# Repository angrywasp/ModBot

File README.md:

# ModBot
Hardware and firmware for a modular robotics system

## Requirements 

PropGCC: https://github.com/angrywasp/propeller-gcc-windows  
Get two command line tools:  
[BSI, the BasicScript interpreter](https://github/com/angrywasp/basicscript). Scripts are written in BasicScript. Follow the link to learn more
PropTool. A basic command line tool for programming the Propeller chip. Compatible with official and unofficial propeller programming hardware
```
dotnet tool install -g AngryWasp.BasicScript.Interpreter
dotnet tool install -g AngryWasp.PropTool
```

Then build the framework
```powershell
bsi ./make.bs --% --run clean()
bsi ./make.bs --% --run buildFramework()
```

Hardware Notes: mn     mn

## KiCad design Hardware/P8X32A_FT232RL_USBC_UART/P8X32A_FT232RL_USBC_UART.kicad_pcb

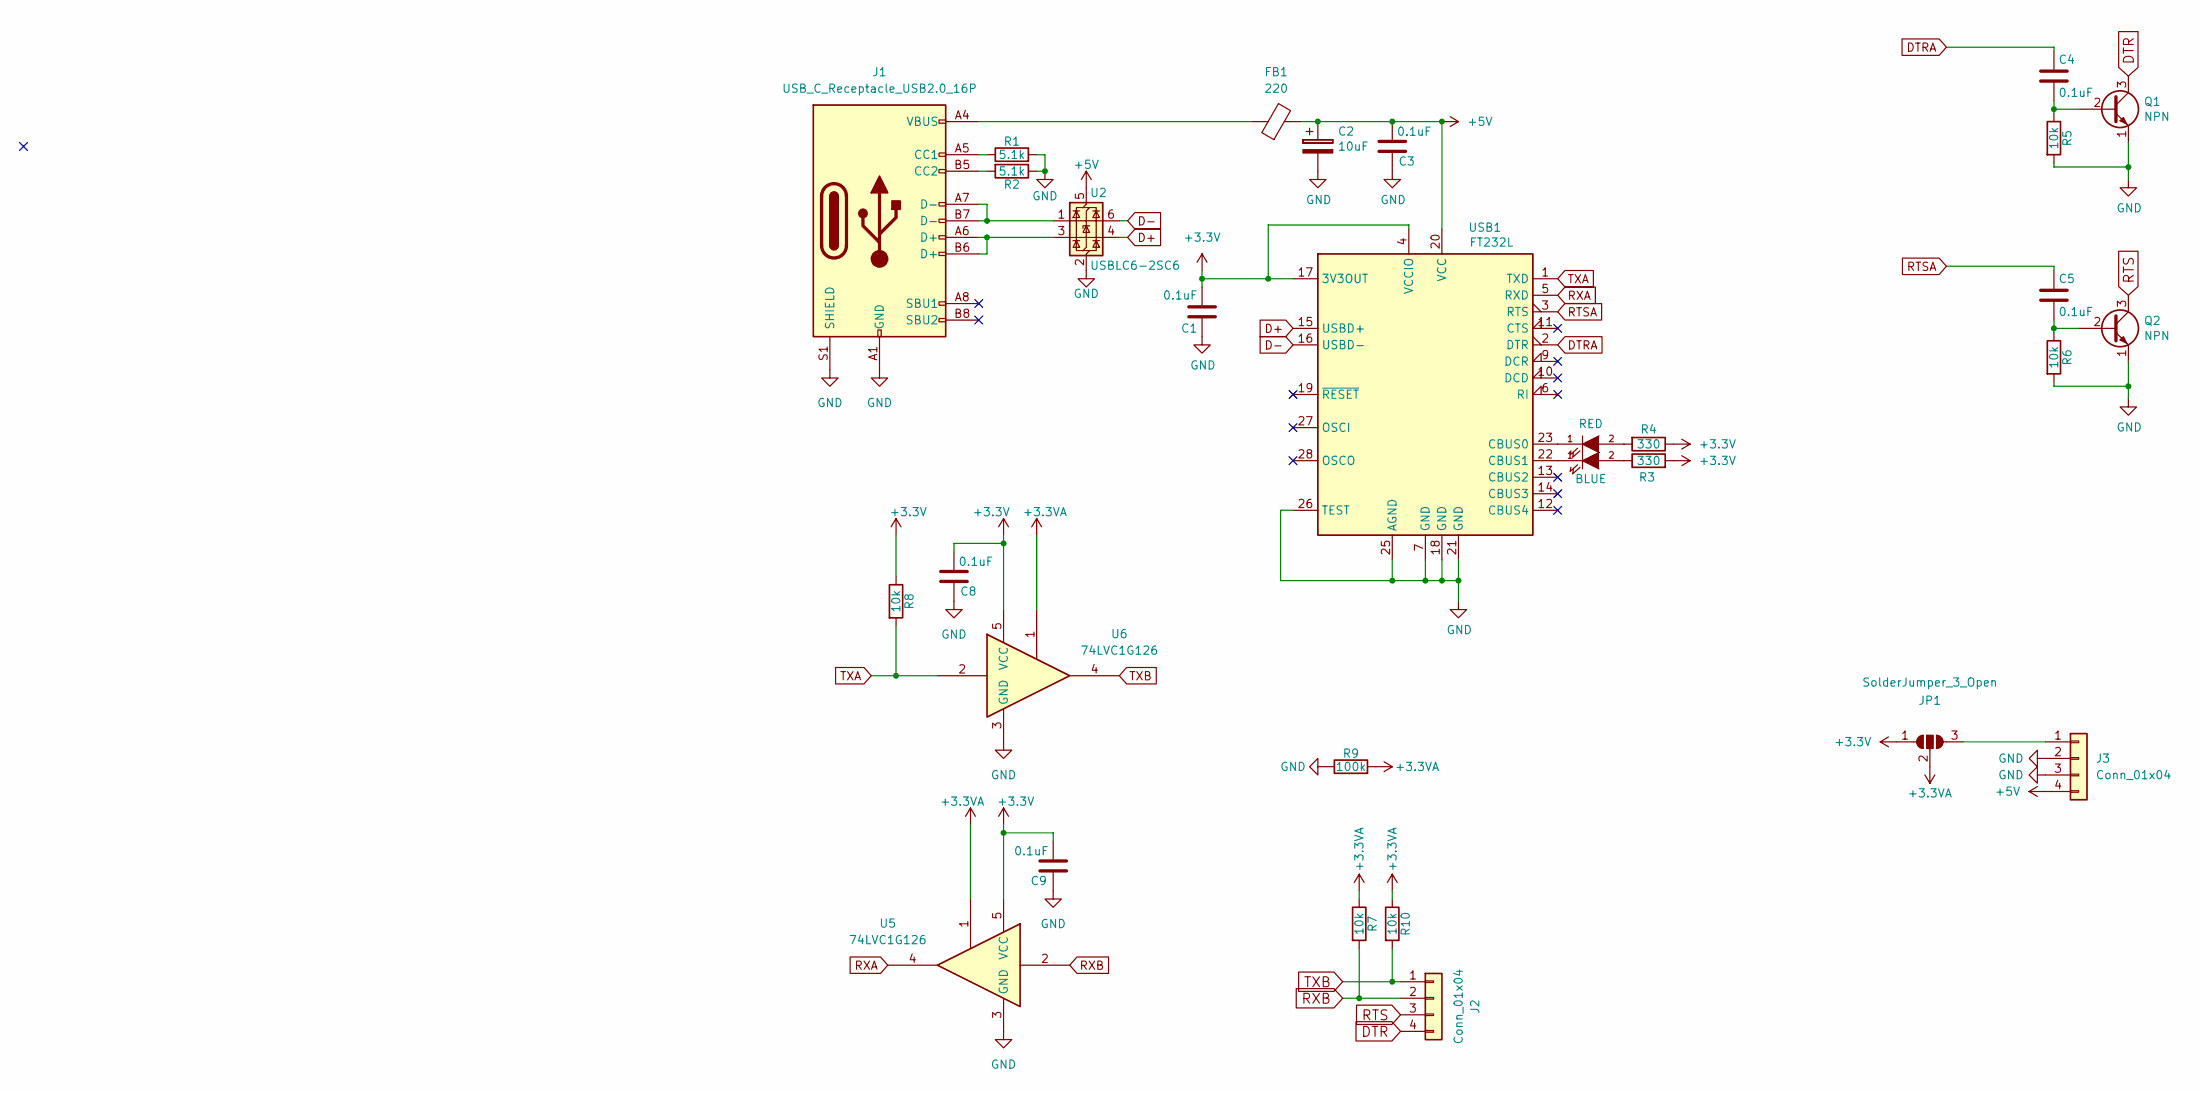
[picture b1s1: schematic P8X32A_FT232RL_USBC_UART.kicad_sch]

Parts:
C1, C3, C4, C5, C8, C9: 0.1uF; C_0805_2012Metric_Pad1.18x1.45mm_HandSolder
C2: 10uF; CP_EIA-3216-18_Kemet-A_HandSolder
D2: BLUE; LED_0805_2012Metric_Pad1.15x1.40mm_HandSolder
D3: RED; LED_0805_2012Metric_Pad1.15x1.40mm_HandSolder
FB1: 220; R_0805_2012Metric_Pad1.20x1.40mm_HandSolder
J1: USB_C_Receptacle_USB2.0_16P; USB_C_Receptacle_HCTL_HC-TYPE-C-16P-01A
J2, J3: Conn_01x04; PinSocket_1x04_P2.54mm_Vertical
JP1: SolderJumper_3_Open; SolderJumper-3_P1.3mm_Open_RoundedPad1.0x1.5mm
Q1, Q2: NPN; SOT-23_Handsoldering
R1, R2: 5.1k; R_0805_2012Metric_Pad1.20x1.40mm_HandSolder
R3, R4: 330; R_0805_2012Metric_Pad1.20x1.40mm_HandSolder
R5, R6, R7, R8, R10: 10k; R_0805_2012Metric_Pad1.20x1.40mm_HandSolder
R9: 100k; R_0805_2012Metric_Pad1.20x1.40mm_HandSolder
U2: USBLC6-2SC6; SOT-23-6
U5, U6: 74LVC1G126; SOT-23-5
USB1: FT232L; SSOP-28_5.3x10.2mm_P0.65mm

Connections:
+3.3V: C1.2, C8.2, C9.2, JP1.1 (A), R3.2, R4.1, R8.1, U5.5 (VCC), U6.5 (VCC), USB1.4 (VCCIO), USB1.17 (3V3OUT)
+3.3VA: JP1.2 (C), R7.1, R9.2, R10.1, U5.1, U6.1
+5V: C2.1, C3.2, FB1.2, J3.4, U2.5 (VBUS), USB1.20 (VCC)
D+: U2.4 (I/O2), USB1.15 (USBD+)
D-: U2.6 (I/O1), USB1.16 (USBD-)
DTR: J2.4, Q1.3 (C)
DTRA: C4.1, USB1.2 (DTR)
GND: C1.1, C2.2, C3.1, C8.1, C9.1, J1.A1 (GND), J1.A12 (GND), J1.B1 (GND), J1.B12 (GND), J1.S1 (SHIELD), J3.2, J3.3, Q1.1 (E), Q2.1 (E), R1.2, R2.1, R5.2, R6.2, R9.1, U2.2 (GND), U5.3 (GND), U6.3 (GND), USB1.7 (GND), USB1.18 (GND), USB1.21 (GND), USB1.25 (AGND), USB1.26 (TEST)
unnamed: D2.2 (A), R3.1
unnamed: D2.1 (K), USB1.22 (CBUS1)
unnamed: D3.2 (A), R4.2
unnamed: D3.1 (K), USB1.23 (CBUS0)
unnamed: FB1.1, J1.A4 (VBUS), J1.A9 (VBUS), J1.B4 (VBUS), J1.B9 (VBUS)
unnamed: J1.A5 (CC1), R1.1
unnamed: J1.B5 (CC2), R2.2
unnamed: J1.A6 (D+), J1.B6 (D+), U2.3 (I/O2)
unnamed: J1.A7 (D-), J1.B7 (D-), U2.1 (I/O1)
unnamed: J3.1, JP1.3 (B)
unnamed: C4.2, Q1.2 (B), R5.1
unnamed: C5.2, Q2.2 (B), R6.1
RTS: J2.3, Q2.3 (C)
RTSA: C5.1, USB1.3 (RTS)
RXA: U5.4, USB1.5 (RXD)
RXB: J2.2, R7.2, U5.2
TXA: R8.2, U6.2, USB1.1 (TXD)
TXB: J2.1, R10.2, U6.4

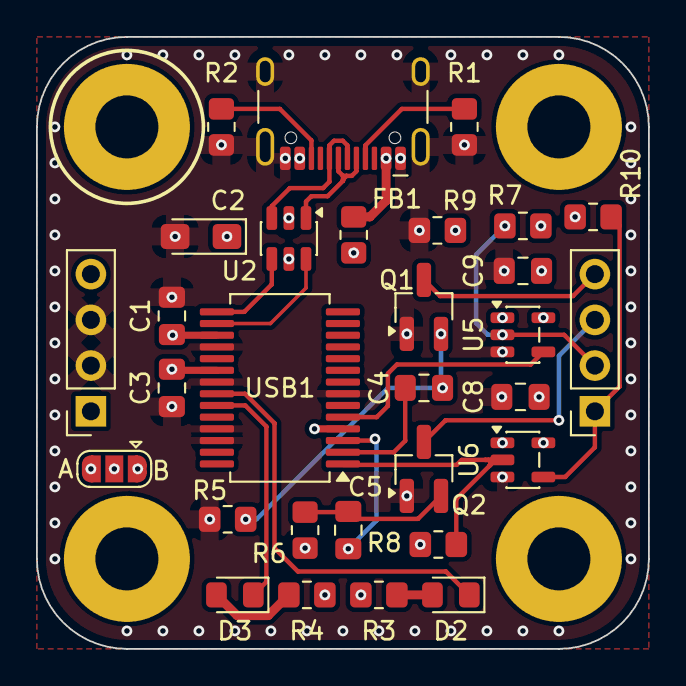
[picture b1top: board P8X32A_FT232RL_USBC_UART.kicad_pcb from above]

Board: 4 copper layers, 34.0 x 34.0 mm, 30 parts (0 on the bottom side), 26 nets.

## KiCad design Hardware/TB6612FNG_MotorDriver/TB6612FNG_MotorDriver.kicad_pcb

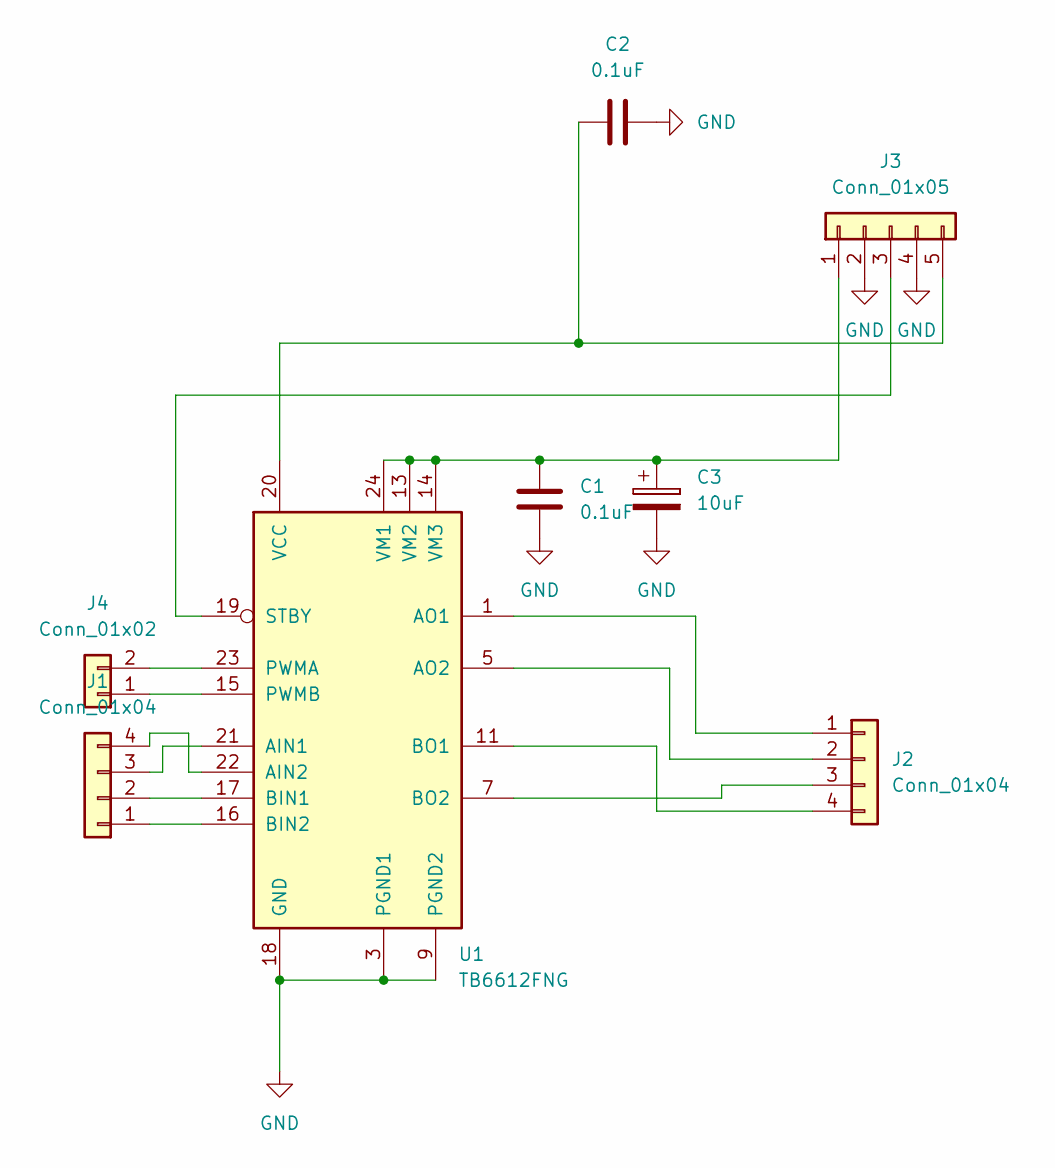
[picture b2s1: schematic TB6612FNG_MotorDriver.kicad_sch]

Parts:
C1, C2: 0.1uF; C_0805_2012Metric_Pad1.18x1.45mm_HandSolder
C3: 10uF; CP_Elec_4x3
J1, J2: Conn_01x04; PinHeader_1x04_P2.54mm_Vertical
J3: Conn_01x05; PinHeader_1x05_P2.54mm_Vertical
J4: Conn_01x02; PinHeader_1x02_P2.54mm_Vertical
U1: TB6612FNG; SSOP-24_5.3x8.2mm_P0.65mm

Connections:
GND: C1.2, C2.2, C3.2, J3.2, J3.4, U1.3 (PGND1), U1.4 (PGND1), U1.9 (PGND2), U1.10 (PGND2), U1.18 (GND)
unnamed: J1.1, U1.16 (BIN2)
unnamed: J1.2, U1.17 (BIN1)
unnamed: J1.3, U1.21 (AIN1)
unnamed: J1.4, U1.22 (AIN2)
unnamed: J2.1, U1.1 (AO1), U1.2 (AO1)
unnamed: J2.2, U1.5 (AO2), U1.6 (AO2)
unnamed: J2.3, U1.7 (BO2), U1.8 (BO2)
unnamed: J2.4, U1.11 (BO1), U1.12 (BO1)
unnamed: C1.1, C3.1, J3.1, U1.13 (VM2), U1.14 (VM3), U1.24 (VM1)
unnamed: J3.3, U1.19 (STBY)
unnamed: C2.1, J3.5, U1.20 (VCC)
unnamed: J4.1, U1.15 (PWMB)
unnamed: J4.2, U1.23 (PWMA)

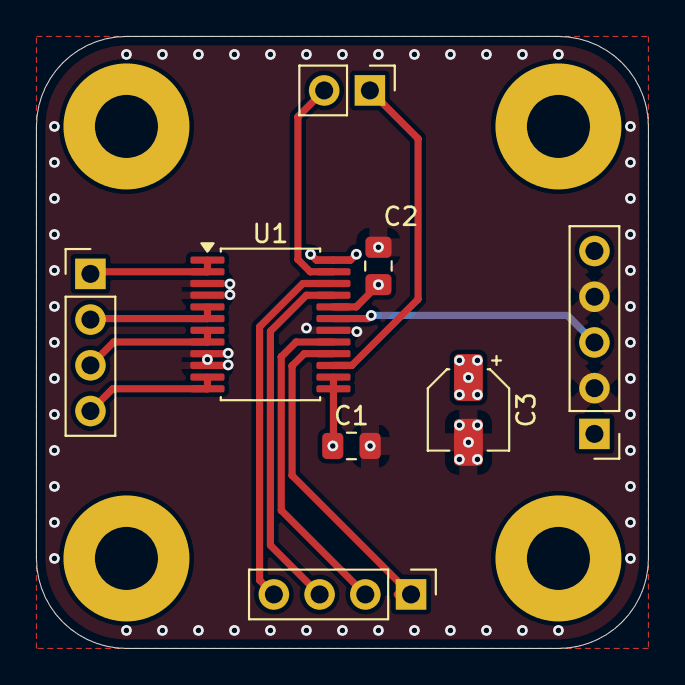
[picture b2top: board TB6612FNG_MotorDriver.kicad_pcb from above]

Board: 4 copper layers, 34.0 x 34.0 mm, 8 parts (0 on the bottom side), 14 nets.

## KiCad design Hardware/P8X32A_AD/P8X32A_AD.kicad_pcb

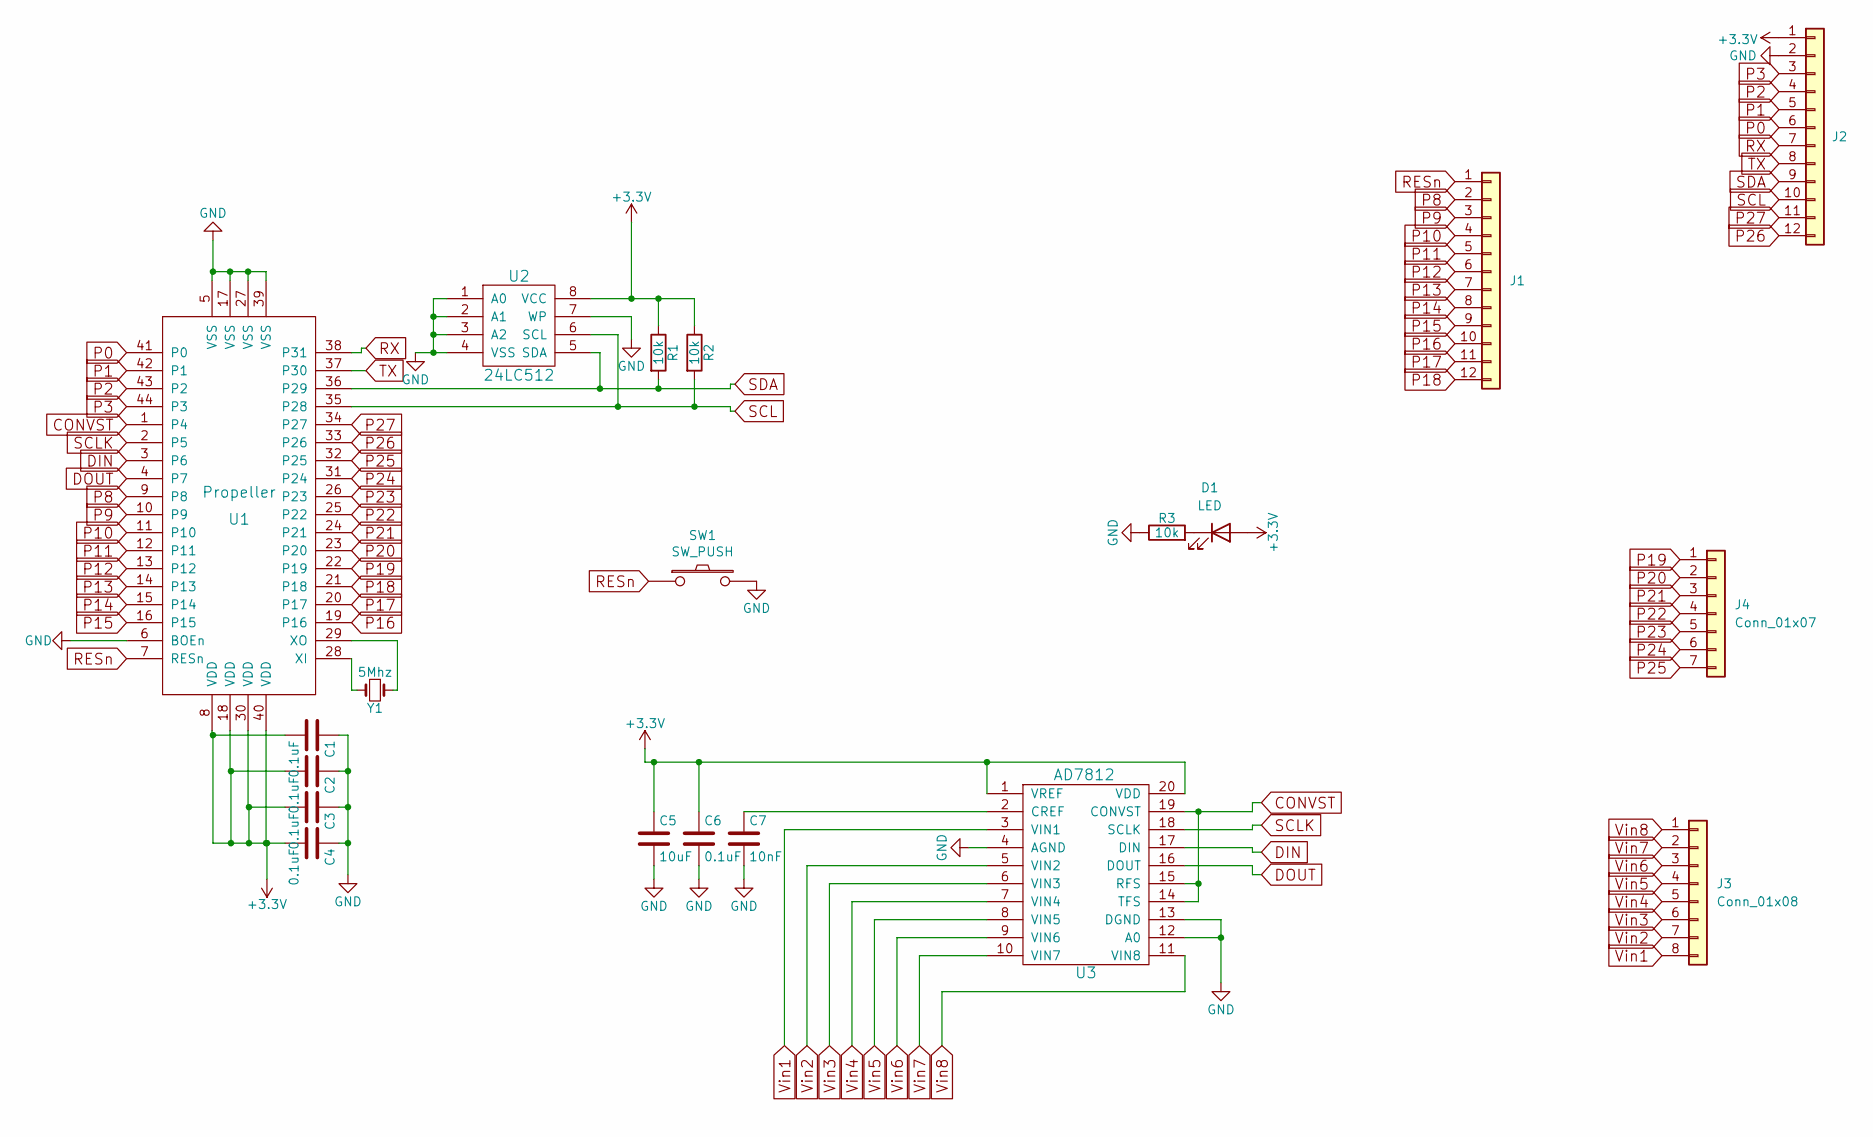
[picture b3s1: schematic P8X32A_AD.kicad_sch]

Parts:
C1, C2, C3, C4, C6: 0.1uF; C_0805_2012Metric_Pad1.18x1.45mm_HandSolder
C5: 10uF; C_0805_2012Metric_Pad1.18x1.45mm_HandSolder
C7: 10nF; C_0805_2012Metric_Pad1.18x1.45mm_HandSolder
D1: LED; LED_0805_2012Metric_Pad1.15x1.40mm_HandSolder
J1, J2: Conn_01x12; PinHeader_1x12_P2.54mm_Vertical
J3: Conn_01x08; PinHeader_1x08_P2.54mm_Vertical
J4: Conn_01x07; PinHeader_1x07_P2.54mm_Vertical
R1, R2, R3: 10k; R_0805_2012Metric_Pad1.20x1.40mm_HandSolder
SW1: SW_PUSH; SW_SPST
U1: Propeller; LQFP-44_10x10mm_P0.8mm
U2: 24LC512; SOIC-8_5.3x5.3mm_P1.27mm
U3: AD7812; Infineon_SOIC-20W_7.6x12.8mm_P1.27mm
Y1: 5Mhz; Crystal_SMD_HC49-SD

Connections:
+3.3V: C1.2, C2.2, C3.2, C4.2, C5.1, C6.1, D1.2 (A), J2.1, R1.1, R2.1, U1.8 (VDD), U1.18 (VDD), U1.30 (VDD), U1.40 (VDD), U2.8 (VCC), U3.1 (VREF), U3.20 (VDD)
CONVST: U1.1 (P4), U3.14 (TFS), U3.15 (RFS), U3.19 (CONVST)
DIN: U1.3 (P6), U3.17 (DIN)
DOUT: U1.4 (P7), U3.16 (DOUT)
GND: C1.1, C2.1, C3.1, C4.1, C5.2, C6.2, C7.2, J2.2, R3.1, SW1.2, U1.5 (VSS), U1.6 (BOEn), U1.17 (VSS), U1.27 (VSS), U1.39 (VSS), U2.1 (A0), U2.2 (A1), U2.3 (A2), U2.4 (VSS), U2.7 (WP), U3.4 (AGND), U3.12 (A0), U3.13 (DGND)
unnamed: D1.1 (K), R3.2
unnamed: U1.28 (XI), Y1.2
unnamed: U1.29 (XO), Y1.1
unnamed: C7.1, U3.2 (CREF)
P0: J2.6, U1.41 (P0)
P1: J2.5, U1.42 (P1)
P2: J2.4, U1.43 (P2)
P3: J2.3, U1.44 (P3)
P8: J1.2, U1.9 (P8)
P9: J1.3, U1.10 (P9)
P10: J1.4, U1.11 (P10)
P11: J1.5, U1.12 (P11)
P12: J1.6, U1.13 (P12)
P13: J1.7, U1.14 (P13)
P14: J1.8, U1.15 (P14)
P15: J1.9, U1.16 (P15)
P16: J1.10, U1.19 (P16)
P17: J1.11, U1.20 (P17)
P18: J1.12, U1.21 (P18)
P19: J4.1, U1.22 (P19)
P20: J4.2, U1.23 (P20)
P21: J4.3, U1.24 (P21)
P22: J4.4, U1.25 (P22)
P23: J4.5, U1.26 (P23)
P24: J4.6, U1.31 (P24)
P25: J4.7, U1.32 (P25)
P26: J2.12, U1.33 (P26)
P27: J2.11, U1.34 (P27)
RESn: J1.1, SW1.1, U1.7 (RESn)
RX: J2.7, U1.38 (P31)
SCL: J2.10, R2.2, U1.35 (P28), U2.6 (SCL)
SCLK: U1.2 (P5), U3.18 (SCLK)
SDA: J2.9, R1.2, U1.36 (P29), U2.5 (SDA)
TX: J2.8, U1.37 (P30)
Vin1: J3.8, U3.3 (VIN1)
Vin2: J3.7, U3.5 (VIN2)
Vin3: J3.6, U3.6 (VIN3)
Vin4: J3.5, U3.7 (VIN4)
Vin5: J3.4, U3.8 (VIN5)
Vin6: J3.3, U3.9 (VIN6)
Vin7: J3.2, U3.10 (VIN7)
Vin8: J3.1, U3.11 (VIN8)

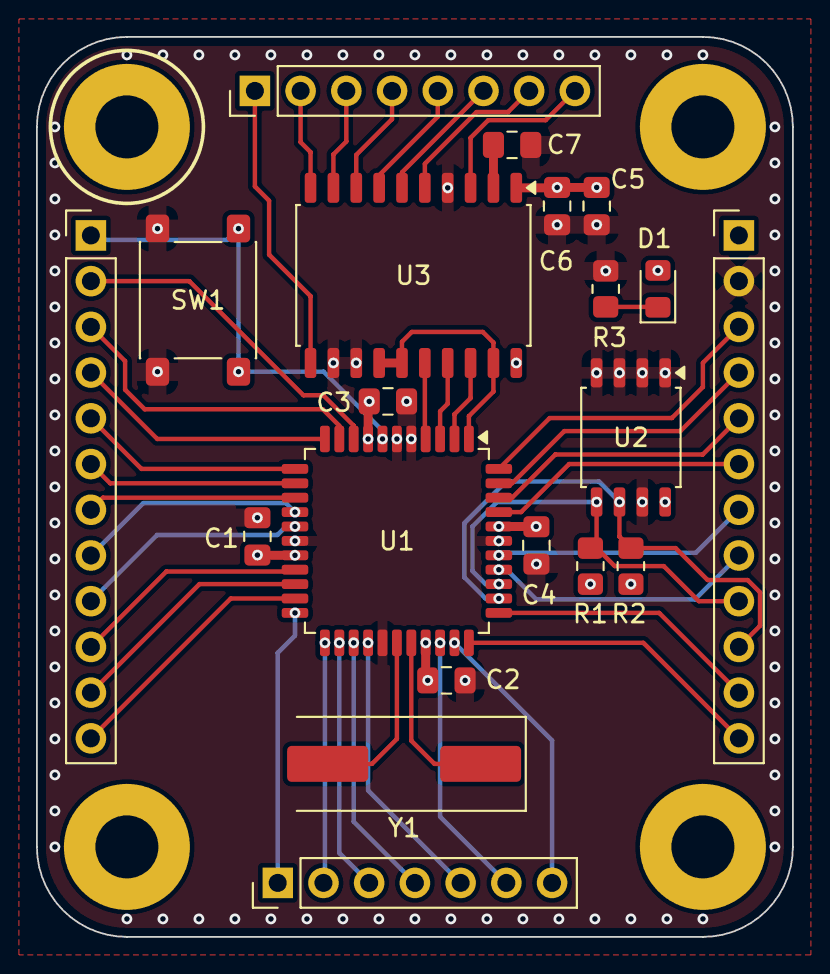
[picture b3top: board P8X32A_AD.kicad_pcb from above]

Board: 4 copper layers, 42.0 x 50.0 mm, 20 parts (0 on the bottom side), 47 nets.

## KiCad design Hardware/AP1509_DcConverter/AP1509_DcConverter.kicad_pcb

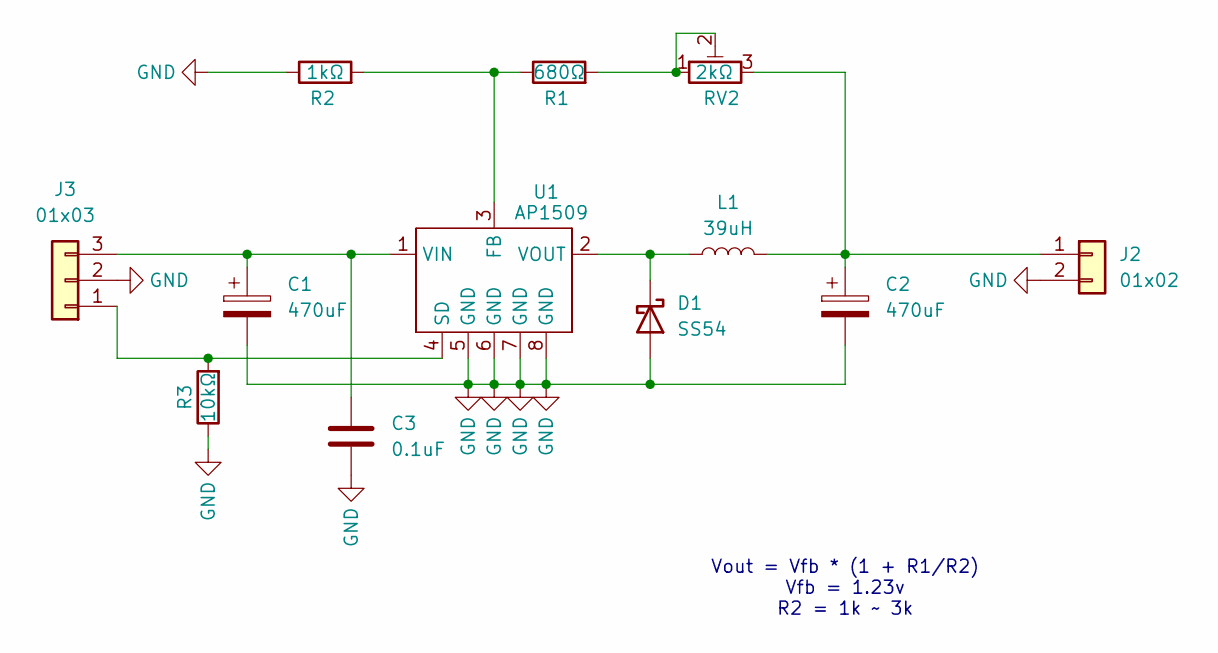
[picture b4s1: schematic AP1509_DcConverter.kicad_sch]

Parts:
C1, C2: 470uF; CP_Elec_8x10.5
C3: 0.1uF; C_0805_2012Metric_Pad1.18x1.45mm_HandSolder
D1: SS54; D_SMB_Handsoldering
J2: 01x02; PinHeader_1x02_P2.54mm_Vertical
J3: 01x03; PinHeader_1x03_P2.54mm_Vertical
L1: 39uH; L_APV_APH0630
R1: 680Ω; R_0805_2012Metric_Pad1.20x1.40mm_HandSolder
R2: 1kΩ; R_0805_2012Metric_Pad1.20x1.40mm_HandSolder
R3: 10kΩ; R_0805_2012Metric_Pad1.20x1.40mm_HandSolder
RV2: 2kΩ; Potentiometer_Bourns_3224W_Vertical
U1: AP1509; SOP-8_3.76x4.96mm_P1.27mm

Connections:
GND: C1.2, C2.2, C3.2, D1.2 (A), J2.2, J3.2, R2.1, R3.1, U1.5 (GND), U1.6 (GND), U1.7 (GND), U1.8 (GND)
unnamed: D1.1 (K), L1.1, U1.2 (VOUT)
unnamed: C2.1, J2.1, L1.2, RV2.3
unnamed: J3.1, R3.2, U1.4 (SD)
unnamed: C1.1, C3.1, J3.3, U1.1 (VIN)
unnamed: R1.2, RV2.1, RV2.2
unnamed: R1.1, R2.2, U1.3 (FB)

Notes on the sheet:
Vout = Vfb * (1 + R1/R2) Vfb = 1.23v R2 = 1k ~ 3k

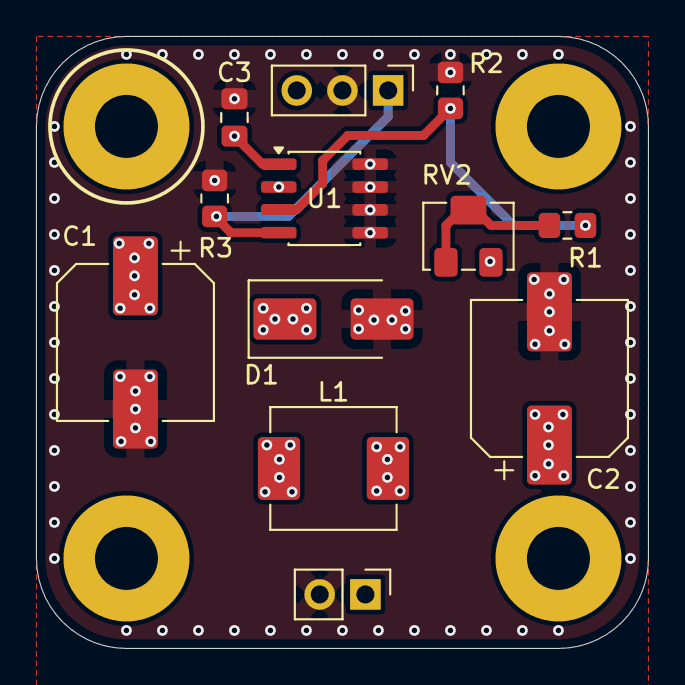
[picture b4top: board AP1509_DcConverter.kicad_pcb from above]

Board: 4 copper layers, 34.0 x 34.0 mm, 12 parts (0 on the bottom side), 7 nets.

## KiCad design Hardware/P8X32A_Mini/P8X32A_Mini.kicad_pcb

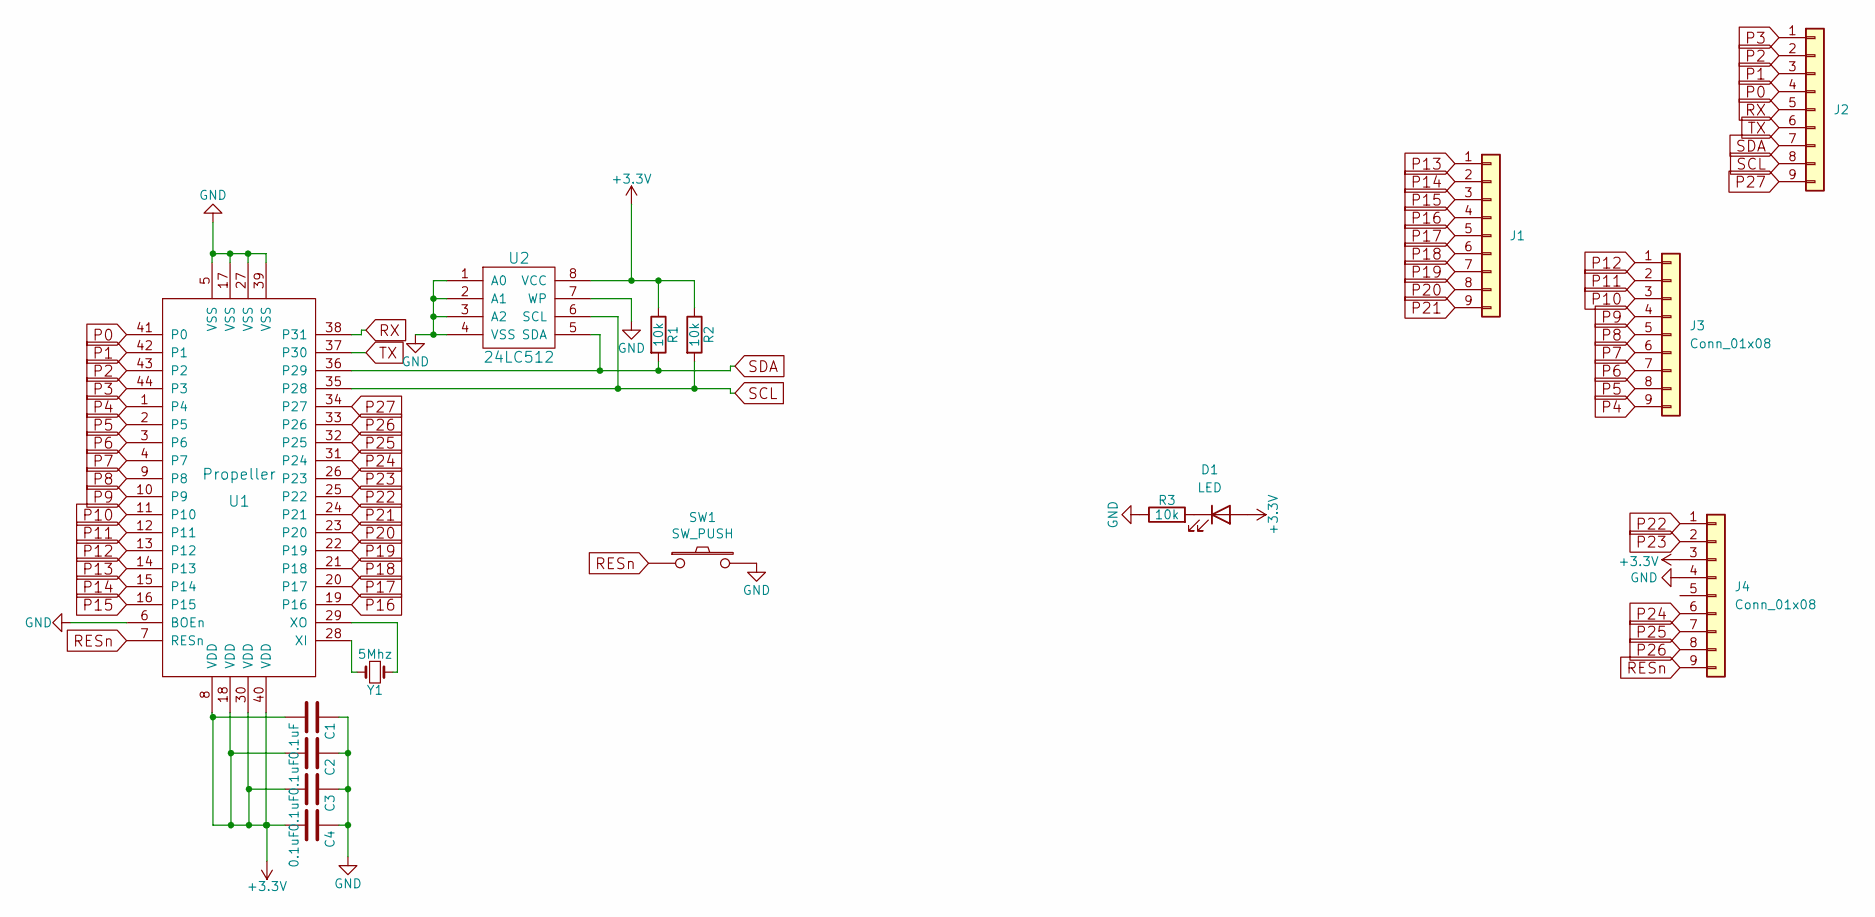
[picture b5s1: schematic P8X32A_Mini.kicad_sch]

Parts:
C1, C2, C3, C4: 0.1uF; C_0805_2012Metric_Pad1.18x1.45mm_HandSolder
D1: LED; LED_0805_2012Metric_Pad1.15x1.40mm_HandSolder
J1, J2: Conn_01x09; PinHeader_1x09_P2.54mm_Vertical
J3, J4: Conn_01x08; PinHeader_1x09_P2.54mm_Vertical
R1, R2, R3: 10k; R_0805_2012Metric_Pad1.20x1.40mm_HandSolder
SW1: SW_PUSH; SW_SPST
U1: Propeller; LQFP-44_10x10mm_P0.8mm
U2: 24LC512; SOIC-8_5.3x5.3mm_P1.27mm
Y1: 5Mhz; Crystal_SMD_HC49-SD

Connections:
+3.3V: C1.2, C2.2, C3.2, C4.2, D1.2 (A), J4.3, R1.1, R2.1, U1.8 (VDD), U1.18 (VDD), U1.30 (VDD), U1.40 (VDD), U2.8 (VCC)
GND: C1.1, C2.1, C3.1, C4.1, J4.4, R3.1, SW1.2, U1.5 (VSS), U1.6 (BOEn), U1.17 (VSS), U1.27 (VSS), U1.39 (VSS), U2.1 (A0), U2.2 (A1), U2.3 (A2), U2.4 (VSS), U2.7 (WP)
unnamed: D1.1 (K), R3.2
unnamed: U1.28 (XI), Y1.2
unnamed: U1.29 (XO), Y1.1
P0: J2.4, U1.41 (P0)
P1: J2.3, U1.42 (P1)
P2: J2.2, U1.43 (P2)
P3: J2.1, U1.44 (P3)
P4: J3.9, U1.1 (P4)
P5: J3.8, U1.2 (P5)
P6: J3.7, U1.3 (P6)
P7: J3.6, U1.4 (P7)
P8: J3.5, U1.9 (P8)
P9: J3.4, U1.10 (P9)
P10: J3.3, U1.11 (P10)
P11: J3.2, U1.12 (P11)
P12: J3.1, U1.13 (P12)
P13: J1.1, U1.14 (P13)
P14: J1.2, U1.15 (P14)
P15: J1.3, U1.16 (P15)
P16: J1.4, U1.19 (P16)
P17: J1.5, U1.20 (P17)
P18: J1.6, U1.21 (P18)
P19: J1.7, U1.22 (P19)
P20: J1.8, U1.23 (P20)
P21: J1.9, U1.24 (P21)
P22: J4.1, U1.25 (P22)
P23: J4.2, U1.26 (P23)
P24: J4.6, U1.31 (P24)
P25: J4.7, U1.32 (P25)
P26: J4.8, U1.33 (P26)
P27: J2.9, U1.34 (P27)
RESn: J4.9, SW1.1, U1.7 (RESn)
RX: J2.5, U1.38 (P31)
SCL: J2.8, R2.2, U1.35 (P28), U2.6 (SCL)
SDA: J2.7, R1.2, U1.36 (P29), U2.5 (SDA)
TX: J2.6, U1.37 (P30)

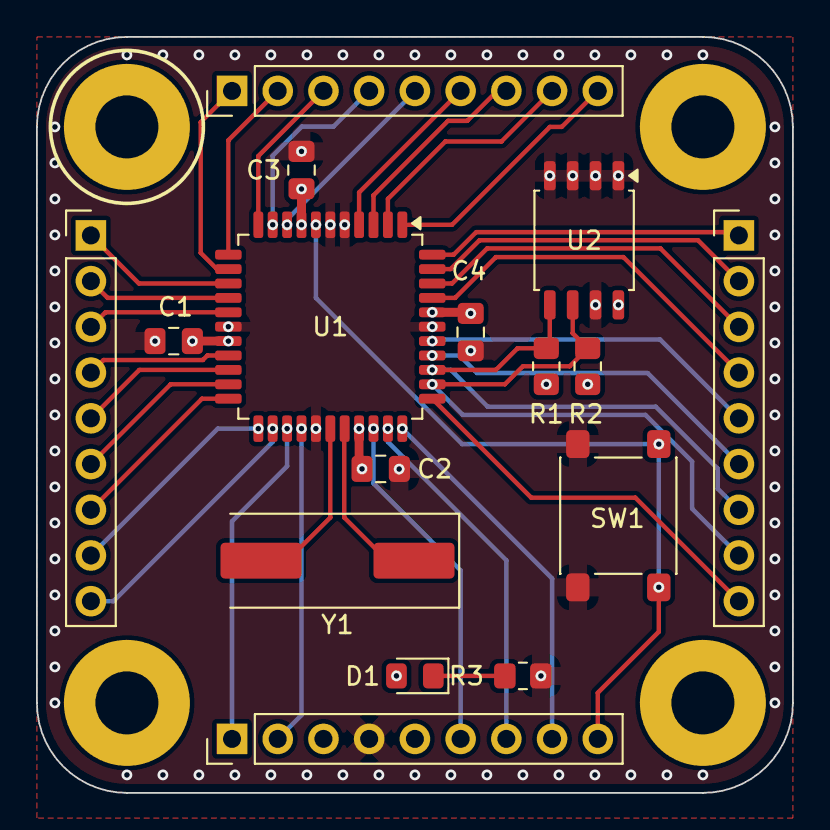
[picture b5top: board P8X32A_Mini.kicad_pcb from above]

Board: 4 copper layers, 42.0 x 42.0 mm, 16 parts (0 on the bottom side), 38 nets.

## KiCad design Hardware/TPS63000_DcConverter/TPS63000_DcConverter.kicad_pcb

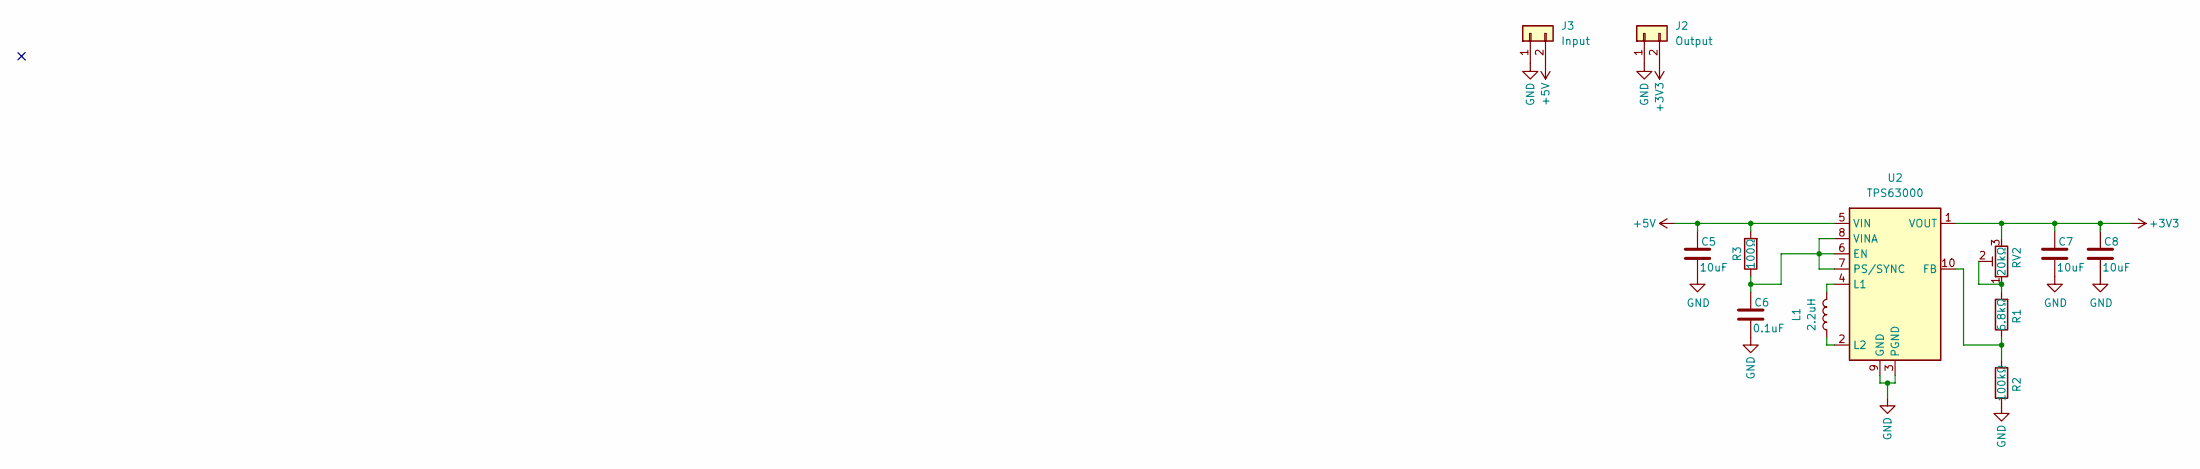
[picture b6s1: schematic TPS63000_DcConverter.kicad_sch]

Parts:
C5, C7, C8: 10uF; C_0805_2012Metric_Pad1.18x1.45mm_HandSolder
C6: 0.1uF; C_0805_2012Metric_Pad1.18x1.45mm_HandSolder
J2: Output; PinSocket_1x02_P2.54mm_Vertical
J3: Input; PinSocket_1x02_P2.54mm_Vertical
L1: 2.2uH; L_APV_APH0530
R1: 6.8kΩ; R_0805_2012Metric_Pad1.20x1.40mm_HandSolder
R2: 100kΩ; R_0805_2012Metric_Pad1.20x1.40mm_HandSolder
R3: 100Ω; R_0805_2012Metric_Pad1.20x1.40mm_HandSolder
RV2: 20kΩ; Potentiometer_Bourns_3224W_Vertical
U2: TPS63000; Texas_DRC0010J_ThermalVias

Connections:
+3V3: C7.1, C8.1, J2.2, RV2.3, U2.1 (VOUT)
+5V: C5.1, J3.2, R3.2, U2.5 (VIN)
GND: C5.2, C6.2, C7.2, C8.2, J2.1, J3.1, R2.1, U2.3 (PGND), U2.9 (GND), U2.11 (PGND)
unnamed: R1.2, RV2.1, RV2.2
unnamed: C6.1, R3.1, U2.6 (EN), U2.7 (PS/SYNC), U2.8 (VINA)
unnamed: R1.1, R2.2, U2.10 (FB)
unnamed: L1.2, U2.4 (L1)
unnamed: L1.1, U2.2 (L2)

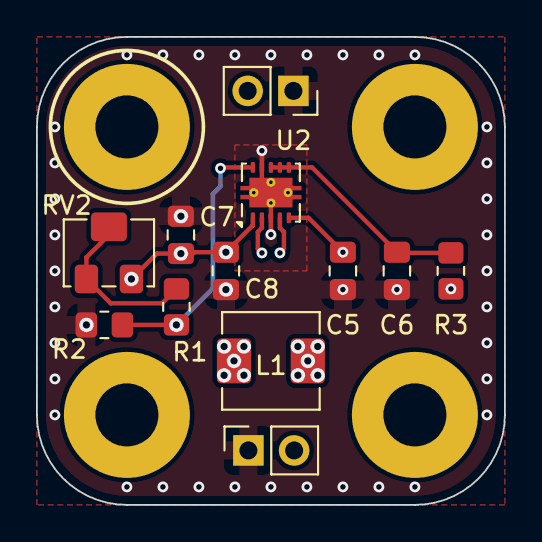
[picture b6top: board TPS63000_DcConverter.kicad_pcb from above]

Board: 4 copper layers, 26.0 x 26.0 mm, 12 parts (0 on the bottom side), 8 nets.

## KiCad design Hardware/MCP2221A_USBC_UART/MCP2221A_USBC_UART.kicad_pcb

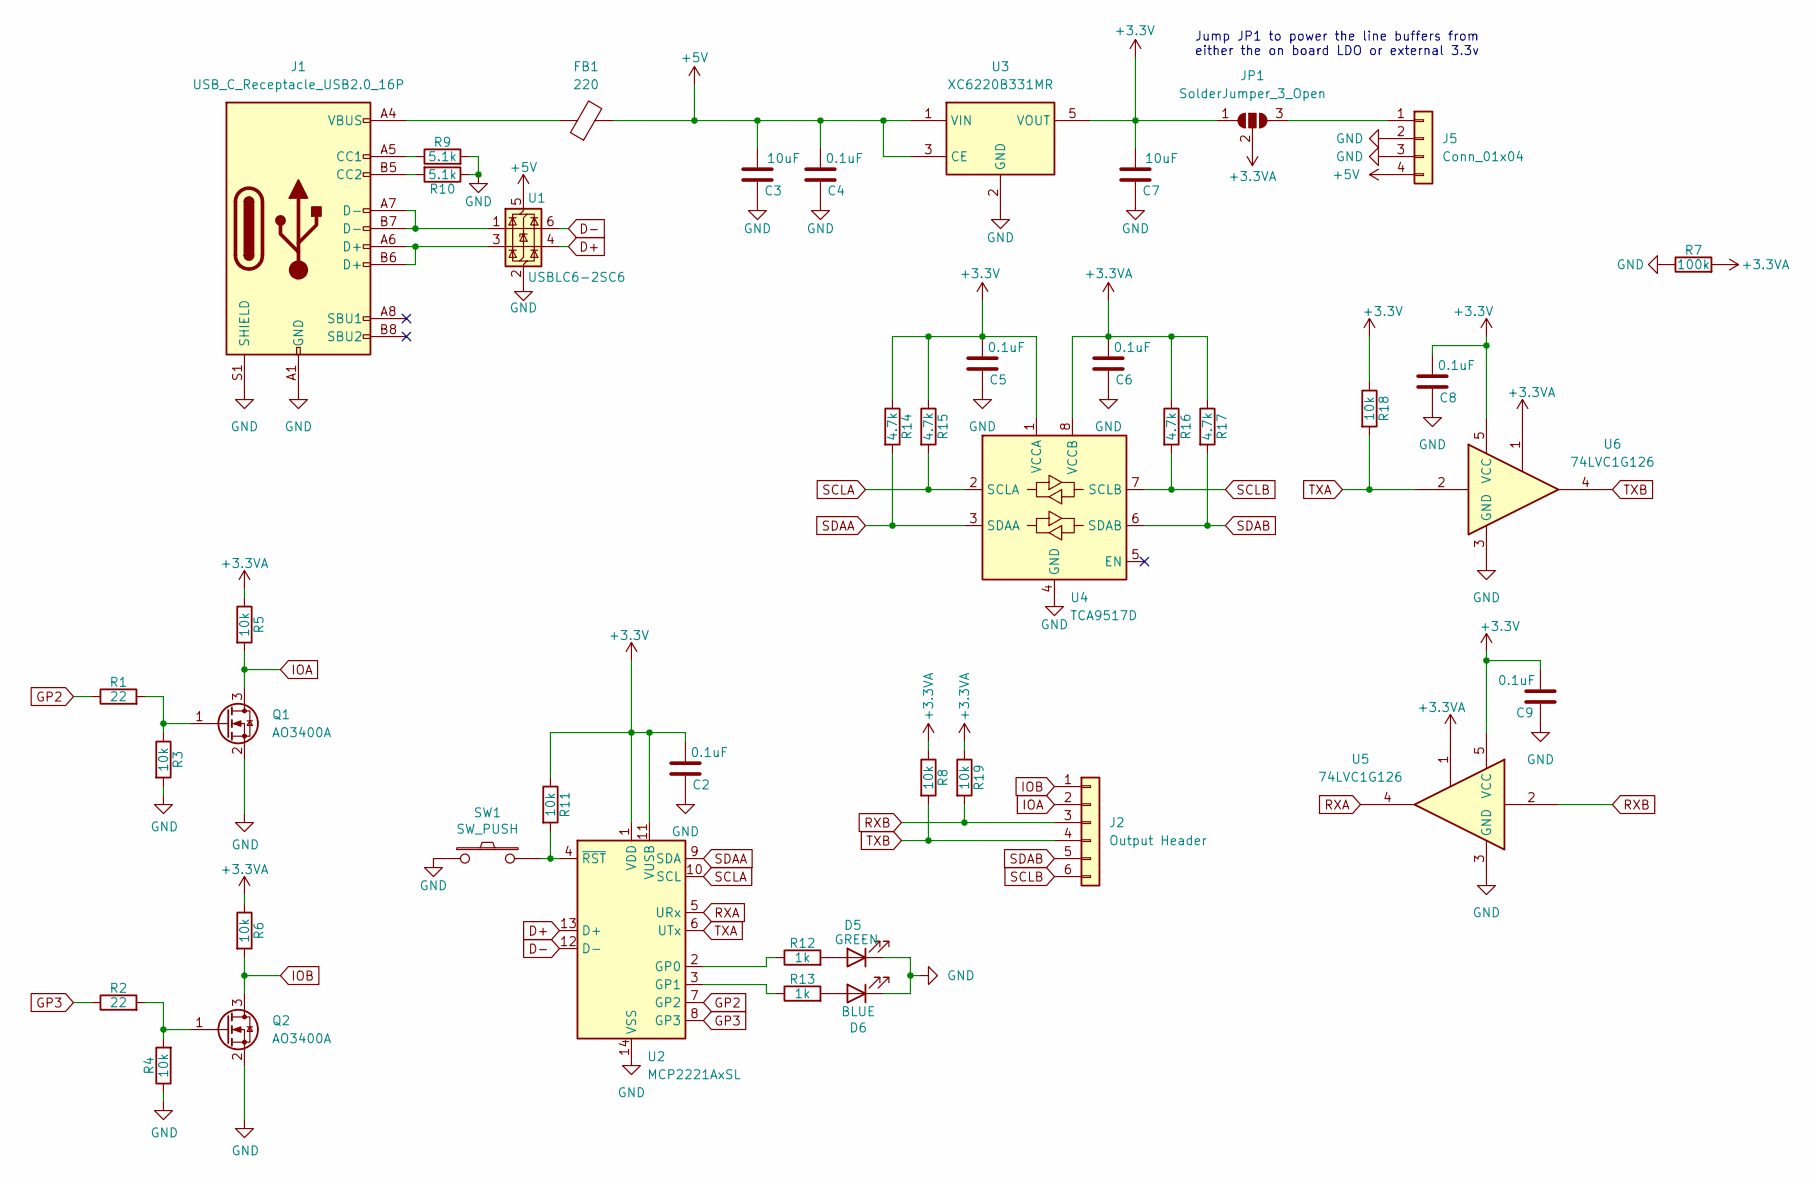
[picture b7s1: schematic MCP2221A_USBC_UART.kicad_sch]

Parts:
C2, C4, C5, C6, C8, C9: 0.1uF; C_0805_2012Metric_Pad1.18x1.45mm_HandSolder
C3, C7: 10uF; C_0805_2012Metric_Pad1.18x1.45mm_HandSolder
D5: GREEN; LED_0805_2012Metric_Pad1.15x1.40mm_HandSolder
D6: BLUE; LED_0805_2012Metric_Pad1.15x1.40mm_HandSolder
FB1: 220; R_0805_2012Metric_Pad1.20x1.40mm_HandSolder
J1: USB_C_Receptacle_USB2.0_16P; USB_C_Receptacle_HCTL_HC-TYPE-C-16P-01A
J2: Output Header; PinHeader_1x06_P2.54mm_Vertical
J5: Conn_01x04; PinSocket_1x04_P2.54mm_Vertical
JP1: SolderJumper_3_Open; SolderJumper-3_P1.3mm_Open_RoundedPad1.0x1.5mm
Q1, Q2: AO3400A; SOT-23
R1, R2: 22; R_0805_2012Metric_Pad1.20x1.40mm_HandSolder
R3, R4, R5, R6, R8, R11, R18, R19: 10k; R_0805_2012Metric_Pad1.20x1.40mm_HandSolder
R7: 100k; R_0805_2012Metric_Pad1.20x1.40mm_HandSolder
R9, R10: 5.1k; R_0805_2012Metric_Pad1.20x1.40mm_HandSolder
R12, R13: 1k; R_0805_2012Metric_Pad1.20x1.40mm_HandSolder
R14, R15, R16, R17: 4.7k; R_0805_2012Metric_Pad1.20x1.40mm_HandSolder
SW1: SW_PUSH; SW_SPST_PTS645Sx43SMTR92
U1: USBLC6-2SC6; SOT-23-6
U2: MCP2221AxSL; SOIC-14_3.9x8.7mm_P1.27mm
U3: XC6220B331MR; SOT-23-5
U4: TCA9517D; SOIC-8_3.9x4.9mm_P1.27mm
U5, U6: 74LVC1G126; SOT-23-5

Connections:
+3.3V: C2.2, C5.2, C7.2, C8.2, C9.2, JP1.1 (A), R11.1, R14.1, R15.1, R18.1, U2.1 (VDD), U2.11 (VUSB), U3.5 (VOUT), U4.1 (VCCA), U5.5 (VCC), U6.5 (VCC)
+3.3VA: C6.2, JP1.2 (C), R5.1, R6.1, R7.2, R8.1, R16.1, R17.1, R19.1, U4.8 (VCCB), U5.1, U6.1
+5V: C3.2, C4.2, FB1.2, J5.4, U1.5 (VBUS), U3.1 (VIN), U3.3 (CE)
D+: U1.4 (I/O2), U2.13 (D+)
D-: U1.6 (I/O1), U2.12 (D-)
GND: C2.1, C3.1, C4.1, C5.1, C6.1, C7.1, C8.1, C9.1, D5.1 (K), D6.1 (K), J1.A1 (GND), J1.A12 (GND), J1.B1 (GND), J1.B12 (GND), J1.S1 (SHIELD), J5.2, J5.3, Q1.2 (S), Q2.2 (S), R3.2, R4.1, R7.1, R9.2, R10.1, SW1.1, U1.2 (GND), U2.14 (VSS), U3.2 (GND), U4.4 (GND), U5.3 (GND), U6.3 (GND)
GP2: R1.1, U2.7 (GP2)
GP3: R2.1, U2.8 (GP3)
IOA: J2.2, Q1.3 (D), R5.2
IOB: J2.1, Q2.3 (D), R6.2
unnamed: D5.2 (A), R12.2
unnamed: D6.2 (A), R13.2
unnamed: FB1.1, J1.A4 (VBUS), J1.A9 (VBUS), J1.B4 (VBUS), J1.B9 (VBUS)
unnamed: J1.A5 (CC1), R9.1
unnamed: J1.B5 (CC2), R10.2
unnamed: J1.A6 (D+), J1.B6 (D+), U1.3 (I/O2)
unnamed: J1.A7 (D-), J1.B7 (D-), U1.1 (I/O1)
unnamed: J5.1, JP1.3 (B)
unnamed: Q1.1 (G), R1.2, R3.1
unnamed: Q2.1 (G), R2.2, R4.2
unnamed: R12.1, U2.2 (GP0)
unnamed: R13.1, U2.3 (GP1)
unnamed: R11.2, SW1.2, U2.4 (~RST)
RXA: U2.5 (URx), U5.4
RXB: J2.3, R19.2, U5.2
SCLA: R15.2, U2.10 (SCL), U4.2 (SCLA)
SCLB: J2.6, R16.2, U4.7 (SCLB)
SDAA: R14.2, U2.9 (SDA), U4.3 (SDAA)
SDAB: J2.5, R17.2, U4.6 (SDAB)
TXA: R18.2, U2.6 (UTx), U6.2
TXB: J2.4, R8.2, U6.4

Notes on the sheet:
Jump JP1 to power the line buffers from either the on board LDO or external 3.3v

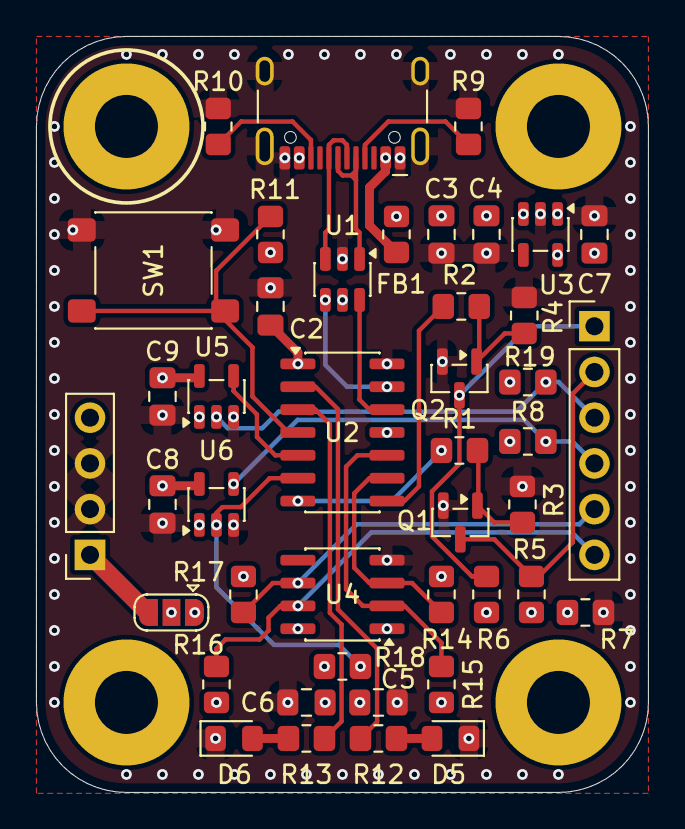
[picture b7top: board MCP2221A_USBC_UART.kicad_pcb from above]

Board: 4 copper layers, 34.0 x 42.0 mm, 43 parts (0 on the bottom side), 31 nets.
